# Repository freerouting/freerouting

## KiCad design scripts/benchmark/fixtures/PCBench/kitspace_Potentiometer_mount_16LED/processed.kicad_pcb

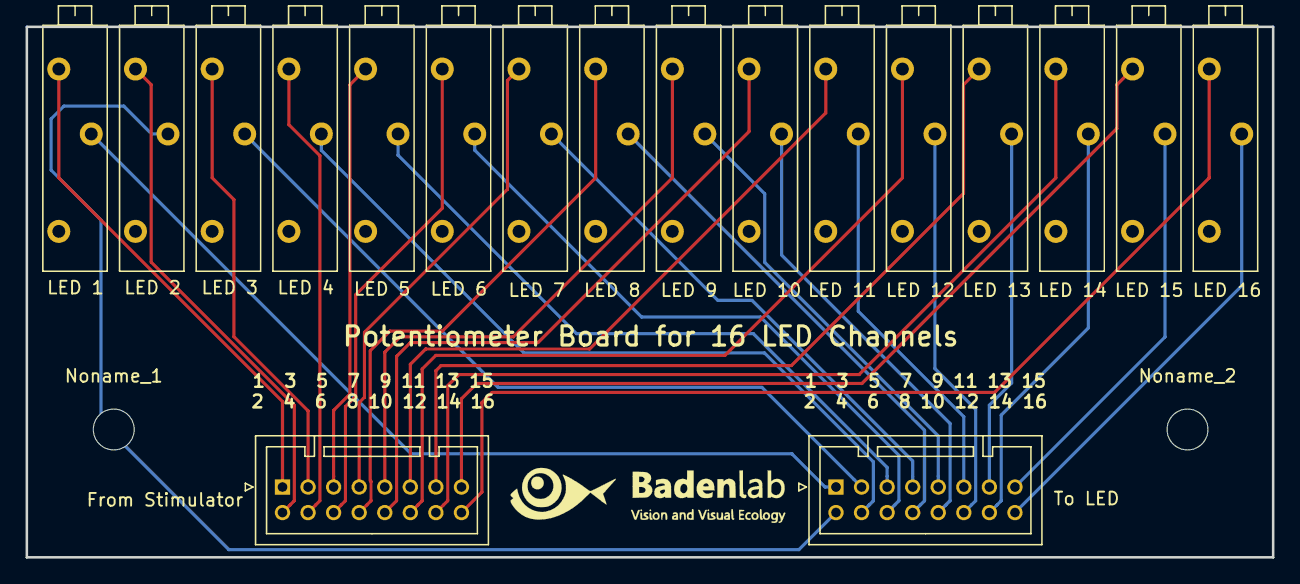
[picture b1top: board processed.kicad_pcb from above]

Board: 2 copper layers, 97.5 x 41.5 mm, 20 parts (0 on the bottom side), 32 nets.

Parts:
 LED 11: R_POT_TRIM; Potentiometer_Vishay_43_Horizontal
From Stimulator: JST_PUD_B16B-PUDSS_2x08_P2.00mm_Vertical
LED 1, LED 2, LED 3, LED 4: Potentiometer_Vishay_43_Horizontal
LED 5, LED 6, LED 7, LED 8, LED 9, LED 10, LED 12, LED 13, LED 14, LED 15, LED 16: R_POT_TRIM; Potentiometer_Vishay_43_Horizontal
Noname_1, Noname_2: MountingHole_3.2mm_M3
To LED: JST_PUD_B16B-PUDSS_2x08_P2.00mm_Vertical

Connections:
unnamed: From Stimulator.1, LED 1.3
unnamed: From Stimulator.2, LED 2.3
unnamed: From Stimulator.3, LED 3.3
unnamed: From Stimulator.4, LED 4.3
unnamed: From Stimulator.5, LED 5.3
unnamed: From Stimulator.6, LED 6.3
unnamed: From Stimulator.7, LED 7.3
unnamed: From Stimulator.8, LED 8.3
unnamed: From Stimulator.9, LED 9.3
unnamed: From Stimulator.10, LED 10.3
unnamed: LED 11.3, From Stimulator.11
unnamed: From Stimulator.12, LED 12.3
unnamed: From Stimulator.13, LED 13.3
unnamed: From Stimulator.14, LED 14.3
unnamed: From Stimulator.15, LED 15.3
unnamed: From Stimulator.16, LED 16.3
unnamed: LED 1.2, To LED.1
unnamed: LED 2.2, To LED.2
unnamed: LED 3.2, To LED.3
unnamed: LED 4.2, To LED.4
unnamed: LED 5.2, To LED.5
unnamed: LED 6.2, To LED.6
unnamed: LED 7.2, To LED.7
unnamed: LED 8.2, To LED.8
unnamed: LED 9.2, To LED.9
unnamed: LED 10.2, To LED.10
unnamed: LED 11.2, To LED.11
unnamed: LED 12.2, To LED.12
unnamed: LED 13.2, To LED.13
unnamed: LED 14.2, To LED.14
unnamed: LED 15.2, To LED.15
unnamed: LED 16.2, To LED.16
